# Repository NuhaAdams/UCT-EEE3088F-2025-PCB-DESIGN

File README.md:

# UCT-EEE3088F-2025-PCB-DESIGN
EEE3088F-MicroMouse Power Subsystem-Group55
# Overall Project
This repository contains the design files, documentation, and supporting resources for the Power Subsystem of the EEE3088F Micro-Mouse course project.
The project involved designing a power board for a micro-mouse maze-solving robot, while the sensing board, processor and motherboard were given.
# The Power Board
The power subsystem is responsible for:
Bidirectional control of 4 motors via H-Bridge drivers (DRV8833PWR).
5V and 3.3V regulated outputs using MC33063AD and TPS62200DBV regulators respectively.
Battery monitoring via INA219 current sensor on the I2C bus.
Battery charging from a USB-C 9V input, with two selectable charging modes (200mA and ~600mA).
High-side switching for two external 5V loads.
System ON/OFF control ensuring <30µA in the OFF state.
The PCB design meets strict budget and dimension constraints, fully interfacing with the Micro-Mouse motherboard.
# How this GitHub repo works
This GitHub repository serves as a central hub for all files related to the power subsystem design of the EEE3088F micro-mouse project.
Each folder in the repository is organized by function. Each of these folders contain the relevant documents that are associated with the design of the power subsystem.

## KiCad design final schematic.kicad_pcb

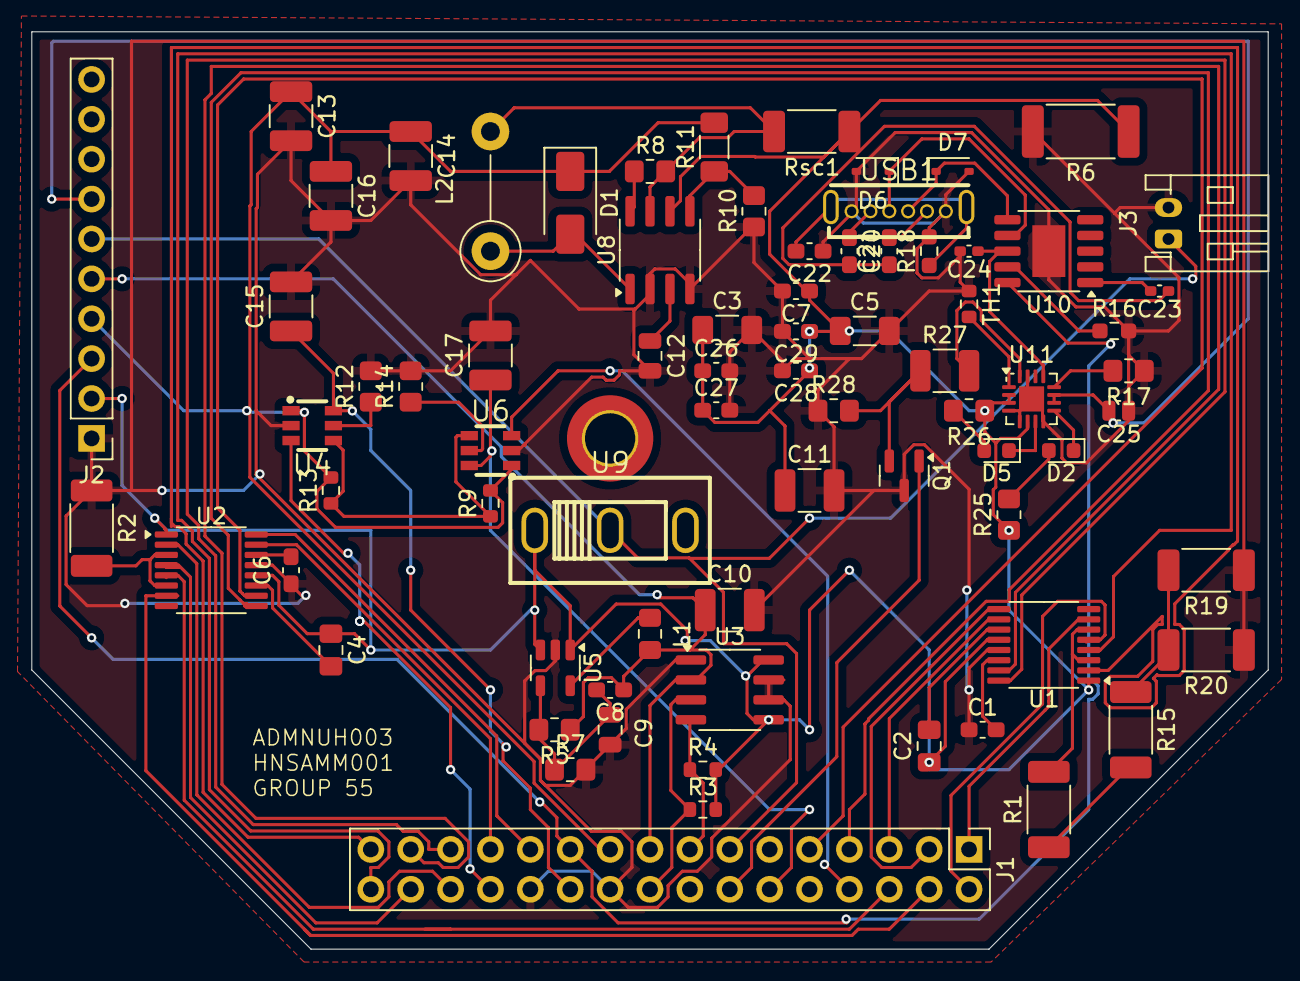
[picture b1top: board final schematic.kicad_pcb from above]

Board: 2 copper layers, 78.7 x 58.4 mm, 75 parts (0 on the bottom side), 65 nets.

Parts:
C1, C6: 2.2u; C_0603_1608Metric_Pad1.08x0.95mm_HandSolder
C2, C4: 0.01u; C_0805_2012Metric_Pad1.18x1.45mm_HandSolder
C3, C5: 10u; C_1206_3216Metric_Pad1.33x1.80mm_HandSolder
C7, C20, C21, C26, C27, C28, C29: 4.7u; C_0603_1608Metric_Pad1.08x0.95mm_HandSolder
C8: 30p; C_0603_1608Metric_Pad1.08x0.95mm_HandSolder
C9: 220p; C_0805_2012Metric
C10, C14, C16: 10u; C_1210_3225Metric_Pad1.33x2.70mm_HandSolder
C11, C13, C15, C17: 100u; C_1210_3225Metric_Pad1.33x2.70mm_HandSolder
C12: 1n; C_0805_2012Metric
C22: 0.47u; C_0603_1608Metric_Pad1.08x0.95mm_HandSolder
C23, C24: 1u; C_0402_1005Metric_Pad0.74x0.62mm_HandSolder
C25: 4.7u; C_0504_1310Metric_Pad0.83x1.28mm_HandSolder
D1: 1N5819; D_SMA
D2, D5: LED; LED_0603_1608Metric
D6, D7: D_SOD-323
J1: Conn_02x16_Odd_Even; PinHeader_2x16_P2.54mm_Vertical
J2: Conn_01x10_Pin; PinHeader_1x10_P2.54mm_Vertical
J3: Conn_01x02; JST_PH_S2B-PH-K_1x02_P2.00mm_Horizontal
L1: 10u; L_0805_2012Metric_Pad1.15x1.40mm_HandSolder
L2: 100u; R_Axial_DIN0411_L9.9mm_D3.6mm_P7.62mm_Vertical
Q1: 2N7002; SOT-23
R1, R2, R15, R19, R20: 0.4; R_2010_5025Metric_Pad1.40x2.65mm_HandSolder
R3, R4: 1.8k; R_0603_1608Metric
R5: 56k; R_0805_2012Metric_Pad1.20x1.40mm_HandSolder
R6: 0.1; R_2512_6332Metric_Pad1.40x3.35mm_HandSolder
R7, R10: 10k; R_0805_2012Metric_Pad1.20x1.40mm_HandSolder
R8: 200; R_0805_2012Metric_Pad1.20x1.40mm_HandSolder
R9, R13: 10k; R_0603_1608Metric
R11: 30k; R_1206_3216Metric_Pad1.30x1.75mm_HandSolder
R12, R14: 24k; R_0805_2012Metric_Pad1.20x1.40mm_HandSolder
R16: 6.8K; R_0603_1608Metric_Pad0.98x0.95mm_HandSolder
R17, R26: 1.2K; R_0805_2012Metric_Pad1.20x1.40mm_HandSolder
R18: 1M; R_0603_1608Metric_Pad0.98x0.95mm_HandSolder
R25: 1.2k; R_0805_2012Metric_Pad1.20x1.40mm_HandSolder
R27: 1.5k; R_1210_3225Metric_Pad1.30x2.65mm_HandSolder
R28: 2.9k; R_0805_2012Metric_Pad1.20x1.40mm_HandSolder
Rsc1: 0.4; R_2010_5025Metric_Pad1.40x2.65mm_HandSolder
TH1: 10k; R_0603_1608Metric
U1, U2: DRV8833PW; TSSOP-16_4.4x5mm_P0.65mm
U3: INA219AxD; SOIC-8_3.9x4.9mm_P1.27mm
U4, U6: TPS2553DBVR; SOT-23-6_L2.9-W1.6-P0.95-LS2.8-BR
U5: TPS62200DBV; SOT-23-5
U8: MC33063AD; SOIC-8_3.9x4.9mm_P1.27mm
U9: HX SS12D10G6; SW-TH_3P-P4.80-HX-SS12D10G4
U10: CH224K; SSOP-10-1EP_3.9x4.9mm_P1mm_EP2.1x3.3mm
U11: BQ24075RGT; VQFN-16-1EP_3x3mm_P0.5mm_EP1.6x1.6mm
USB1: TYPE-C 6P LCH10.0; USB-TH_TYPE-C-6P-LCH10.0

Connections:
3V3 Out: C8.1, C10.1, J1.17, J2.5, L1.2, R5.1, U3.2 (A0)
5V Out: C13.1, C14.1, C16.1, D1.1 (K), J1.19, J2.4, R9.2, R11.2, R13.2, U4.1 (IN), U6.1 (IN)
BATTERY: J1.13, J2.6, J3.1, U9.2
CC1: D6.1 (K), U10.7 (CC1), USB1.A5 (CC1)
CC2: D7.1 (K), U10.6 (CC2), USB1.B5 (CC2)
CTRL_EXT_LOAD1: J1.26, U4.3 (EN)
CTRL_EXT_LOAD2: J1.8, U6.3 (EN)
ChargerOut: C25.2, J2.7, U11.10 (OUT), U11.11 (OUT)
EXT_LOAD1_OUT: C15.1, J1.22, U4.6 (OUT)
EXT_LOAD2_OUT: C17.1, J1.12, U6.6 (OUT)
FAST_CHARGE_CTRL: J1.14, Q1.1 (G)
FAULT_SIGNAL_1: R9.1, R13.1, U4.4 (~FAULT), U6.4 (~FAULT)
GND: C1.1, C3.2, C5.2, C6.1, C7.2, C9.2, C10.2, C11.2, C12.2, C13.2, C14.2, C15.2, C16.2, C17.2, C22.1, C24.2, C25.1, C26.2, C27.2, C28.2, C29.2, D6.2 (A), D7.2 (A), J1.20, J1.24, J2.1, J3.2, Q1.3 (D), R2.1, R6.2, R7.2, R10.1, R12.2, R14.2, R16.2, R17.1, R18.2, R19.1, R20.1, R28.1, TH1.1, U1.13 (GND), U2.13 (GND), U3.1 (A1), U3.6 (GND), U3.7 (IN-), U4.2 (GND), U5.2 (GND), U6.2 (GND), U8.2 (SwE), U8.4 (GND), U10.11 (GND), U11.4 (~CE), U11.5 (EN2), U11.8 (VSS), U11.15 (SYSOFF), U11.17 (VSS), USB1.A12 (GND), USB1.B12 (GND)
HV: J1.21, J2.3, U10.10 (PG)
I2C1_SCL: J1.15, R4.1, U3.4 (SCL)
I2C1_SDA: J1.18, R3.1, U3.3 (SDA)
MOTOR1_A_OUT: J1.31, U1.2 (AOUT1)
MOTOR1_B_OUT: J1.32, U1.4 (AOUT2)
MOTOR1_CTRL1: J1.27, U1.16 (AIN1)
MOTOR1_CTRL2: J1.29, U1.15 (AIN2)
MOTOR2_CTRL1: J1.3, U1.9 (BIN1)
MOTOR2_CTRL2: J1.5, U1.10 (BIN2)
MOTOR3_A_OUT: J1.28, U2.2 (AOUT1)
MOTOR3_B_OUT: J1.30, U2.4 (AOUT2)
MOTOR3_CTRL1: J1.23, U2.16 (AIN1)
MOTOR3_CTRL2: J1.25, U2.15 (AIN2)
MOTOR4_CTRL1: J1.7, U2.9 (BIN1)
MOTOR4_CTRL2: J1.9, U2.10 (BIN2)
Motor2_A_OUT: J1.1, U1.7 (BOUT1)
Motor2_B_OUT: J1.2, U1.5 (BOUT2)
Motor4_A_OUT: J1.4, U2.7 (BOUT1)
Motor4_B_OUT: J1.6, U2.5 (BOUT2)
unnamed: C20.1, USB1.A9 (VBUS)
unnamed: C21.2, USB1.B9 (VBUS)
unnamed: C22.2, R18.1, USB1.7 (EH), USB1.8 (EH)
unnamed: D1.2 (A), L2.1, U8.1 (SwC)
unnamed: D2.2 (A), R25.2
unnamed: D2.1 (K), U11.9 (~CHG)
unnamed: D5.2 (A), R26.2
unnamed: D5.1 (K), U11.7 (~PGOOD)
unnamed: Q1.2 (S), R27.1, R28.2
unnamed: R1.1, R15.2
unnamed: R15.1, R19.2, R20.2
unnamed: R1.2, U1.3 (AISEN), U1.6 (BISEN)
unnamed: C2.2, U1.11 (VCP)
unnamed: C1.2, U1.14 (VINT)
unnamed: R2.2, U2.3 (AISEN), U2.6 (BISEN)
unnamed: C4.2, U2.11 (VCP)
unnamed: C6.2, U2.14 (VINT)
unnamed: R12.1, U4.5 (ILIM)
unnamed: C8.2, C9.1, R5.2, R7.1, U5.4 (FB)
unnamed: L1.1, U5.5 (SW)
unnamed: R14.1, U6.5 (ILIM)
unnamed: R8.1, U8.8 (DC)
unnamed: L2.2, R8.2, Rsc1.2, U8.7 (Ipk)
unnamed: C12.1, U8.3 (TC)
unnamed: R10.2, R11.1, U8.5 (Vfb)
unnamed: R16.1, U10.9 (CFG1)
unnamed: C23.2, U10.1 (VDD)
unnamed: R17.2, U11.12 (ILIM)
unnamed: R27.2, U11.16 (ISET)
unnamed: TH1.2, U11.1 (TS)
SWITCH_INPUT: C2.1, C3.1, C4.1, C5.1, C7.1, C11.1, C26.1, C27.1, C28.1, C29.1, J2.2, R3.2, R4.2, R6.1, R25.1, R26.1, Rsc1.1, U1.1 (nSLEEP), U1.12 (VM), U2.1 (nSLEEP), U2.12 (VM), U3.5 (VS), U3.8 (IN+), U5.1 (VI), U5.3 (EN), U8.6 (Vin), U9.1, U11.2 (BAT), U11.3 (BAT), U11.6 (EN1)
USB C: C20.2, C21.1, C23.1
V_BUS: C24.1, U10.8 (VBUS), U11.13 (IN)
